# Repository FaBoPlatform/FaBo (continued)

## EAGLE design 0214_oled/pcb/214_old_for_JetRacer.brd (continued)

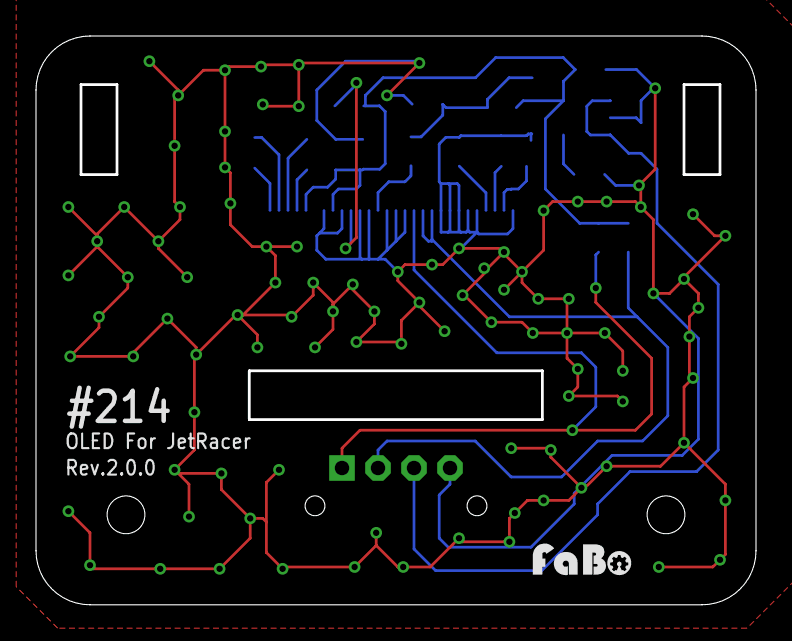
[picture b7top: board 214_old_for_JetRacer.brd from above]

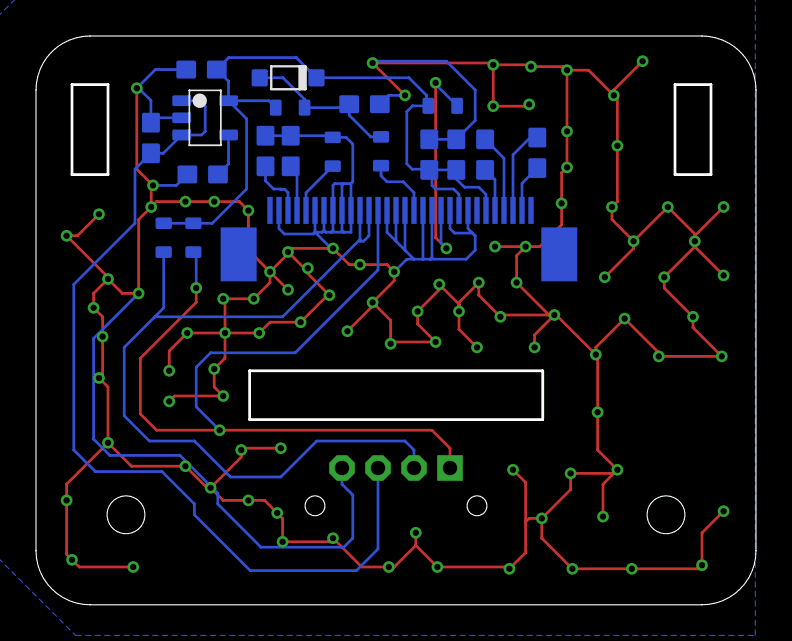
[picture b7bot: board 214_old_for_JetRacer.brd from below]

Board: 2 copper layers, 40.0 x 31.6 mm, 21 parts (18 on the bottom side), 16 nets.

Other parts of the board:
U$1: LOGO_FABO_S
